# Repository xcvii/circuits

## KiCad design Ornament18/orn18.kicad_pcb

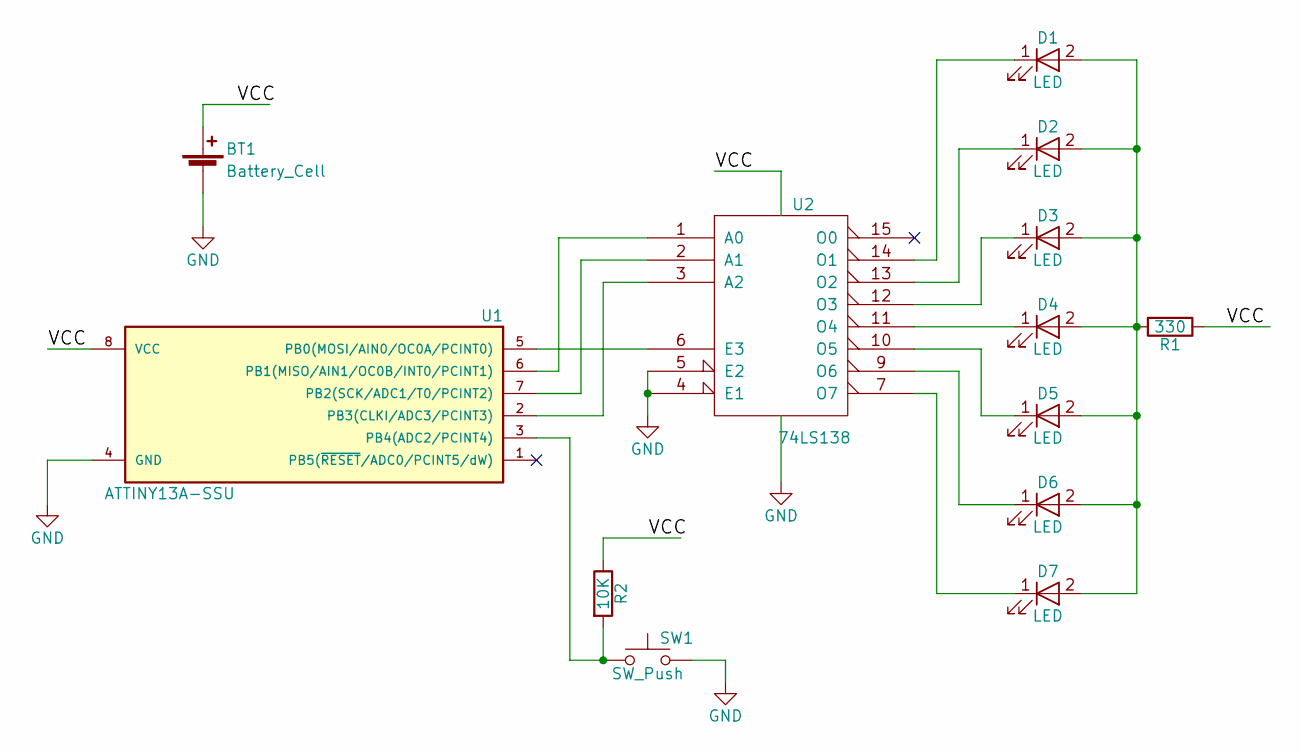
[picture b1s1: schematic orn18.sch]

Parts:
BT1: Battery_Cell; Keystone_3035
D1, D2, D3, D4, D5, D6, D7: LED; LED_0805_HandSoldering
R1: 330; R_0805_HandSoldering
R2: 10K; R_0805_HandSoldering
SW1: SW_Push; Tactile_Switch_6mm_x_6mm
U1: ATTINY13A-SSU; SOIC-8_3.9x4.9mm_Pitch1.27mm
U2: 74LS138; SOIC-16_3.9x9.9mm_Pitch1.27mm

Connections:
GND: BT1.2 (-), SW1.2, U1.4 (GND), U2.4 (E1), U2.5 (E2), U2.8 (GND)
unnamed: D1.1 (K), U2.14 (O1)
unnamed: D1.2 (A), D2.2 (A), D3.2 (A), D4.2 (A), D5.2 (A), D6.2 (A), D7.2 (A), R1.2
unnamed: D2.1 (K), U2.13 (O2)
unnamed: D3.1 (K), U2.12 (O3)
unnamed: D4.1 (K), U2.11 (O4)
unnamed: D5.1 (K), U2.10 (O5)
unnamed: D6.1 (K), U2.9 (O6)
unnamed: D7.1 (K), U2.7 (O7)
unnamed: R2.2, SW1.1, U1.3 (PB4(ADC2/PCINT4))
unnamed: U1.2 (PB3(CLKI/ADC3/PCINT3)), U2.3 (A2)
unnamed: U1.5 (PB0(MOSI/AIN0/OC0A/PCINT0)), U2.6 (E3)
unnamed: U1.6 (PB1(MISO/AIN1/OC0B/INT0/PCINT1)), U2.1 (A0)
unnamed: U1.7 (PB2(SCK/ADC1/T0/PCINT2)), U2.2 (A1)
VCC: BT1.1 (+), R1.1, R2.1, U1.8 (VCC), U2.16 (VCC)

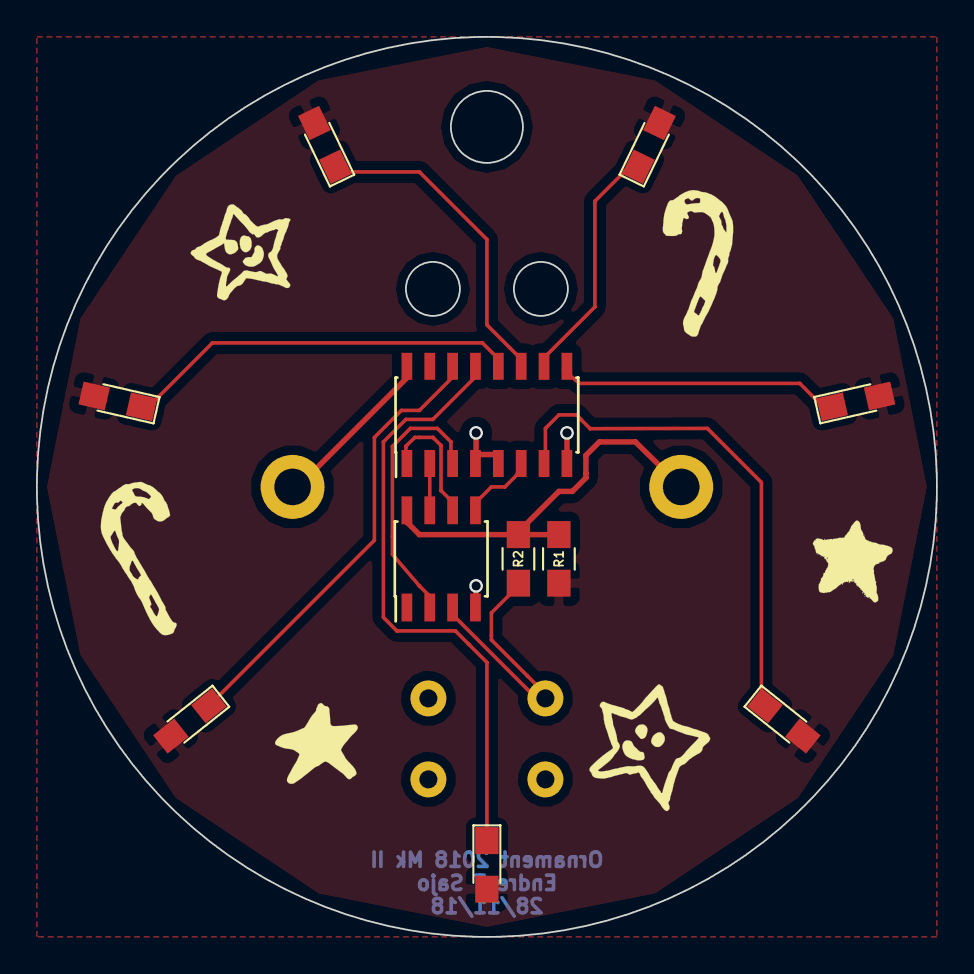
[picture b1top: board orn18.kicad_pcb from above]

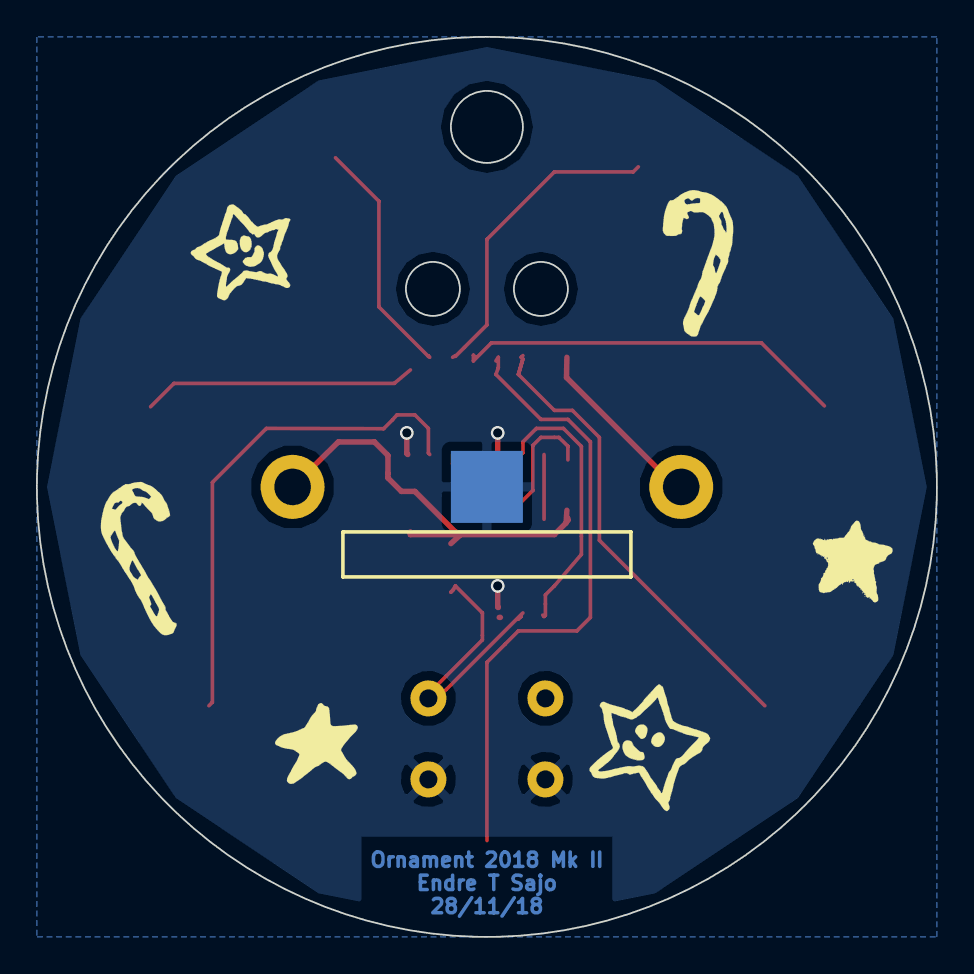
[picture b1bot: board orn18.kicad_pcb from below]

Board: 2 copper layers, 50.0 x 50.0 mm, 13 parts (2 on the bottom side), 15 nets.

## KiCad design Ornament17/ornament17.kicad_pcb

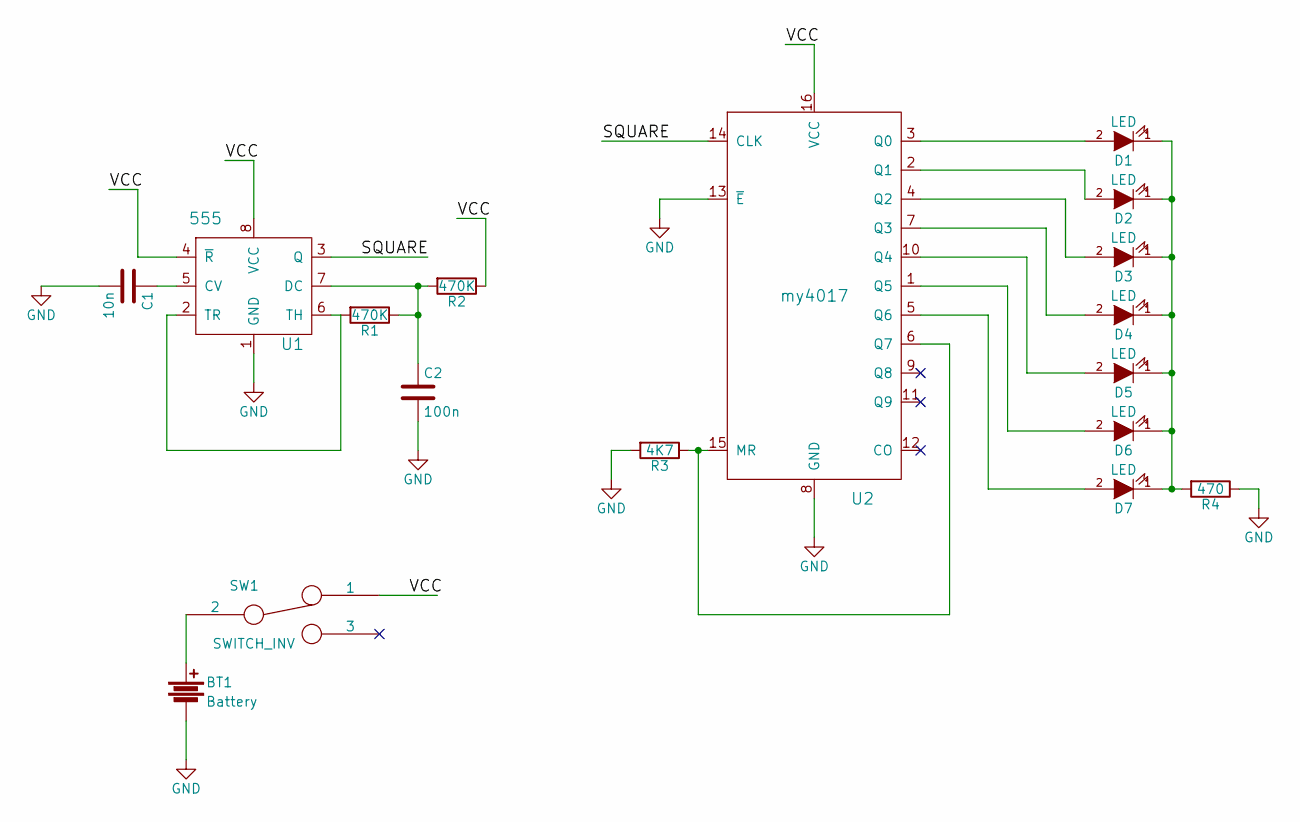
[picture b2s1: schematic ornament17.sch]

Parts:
BT1: Battery; 20mm_battery_clip
C1: 10n; C_0805_HandSoldering
C2: 100n; C_0805_HandSoldering
D1, D2, D3, D4, D5, D6, D7: LED; LED_0805_HandSoldering
R1, R2: 470K; R_0805_HandSoldering
R3: 4K7; R_0805_HandSoldering
R4: 470; R_0805_HandSoldering
SW1: SWITCH_INV; SPDT
U1: 555; SOIC-8_3.9x4.9mm_Pitch1.27mm
U2: my4017; SOIC-16_3.9x9.9mm_Pitch1.27mm

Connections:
/SQUARE: U1.3 (Q), U2.14 (CLK)
/VCC: R2.1, SW1.1, U1.4 (~R), U1.8 (VCC), U2.16 (VCC)
GND: BT1.2, C1.2, C2.2, R3.2, R4.1, U1.1 (GND), U2.8 (GND), U2.13 (~E)
unnamed: BT1.1, SW1.2
unnamed: C1.1, U1.5 (CV)
unnamed: C2.1, R1.1, R2.2, U1.7 (DC)
unnamed: D1.1 (K), D2.1 (K), D3.1 (K), D4.1 (K), D5.1 (K), D6.1 (K), D7.1 (K), R4.2
unnamed: D1.2 (A), U2.3 (Q0)
unnamed: D2.2 (A), U2.2 (Q1)
unnamed: D3.2 (A), U2.4 (Q2)
unnamed: D4.2 (A), U2.7 (Q3)
unnamed: D5.2 (A), U2.10 (Q4)
unnamed: D6.2 (A), U2.1 (Q5)
unnamed: D7.2 (A), U2.5 (Q6)
unnamed: R1.2, U1.2 (TR), U1.6 (TH)
unnamed: R3.1, U2.6 (Q7), U2.15 (MR)

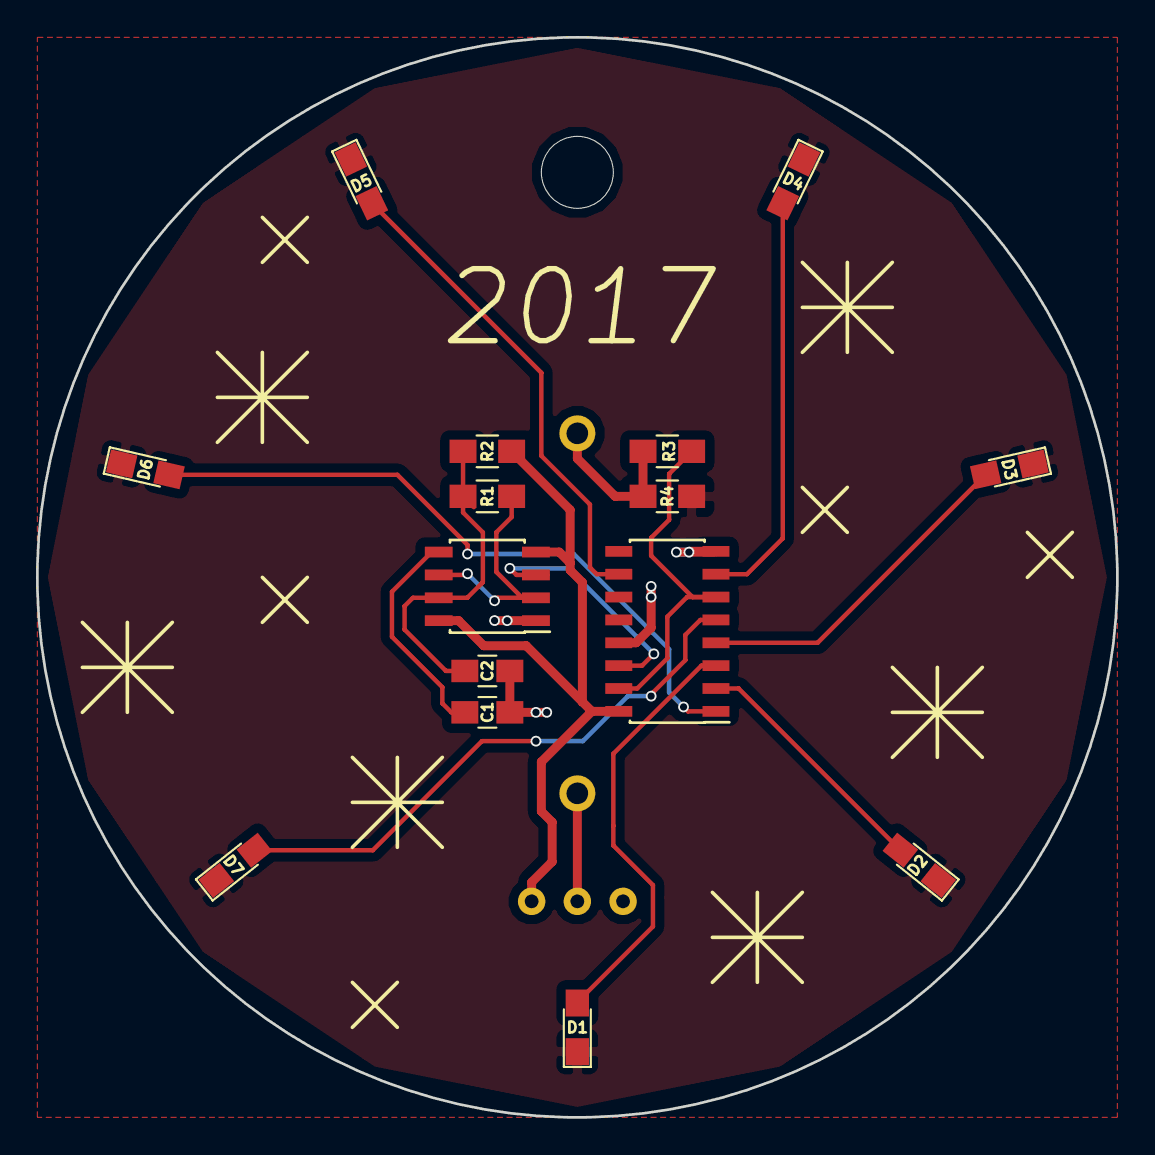
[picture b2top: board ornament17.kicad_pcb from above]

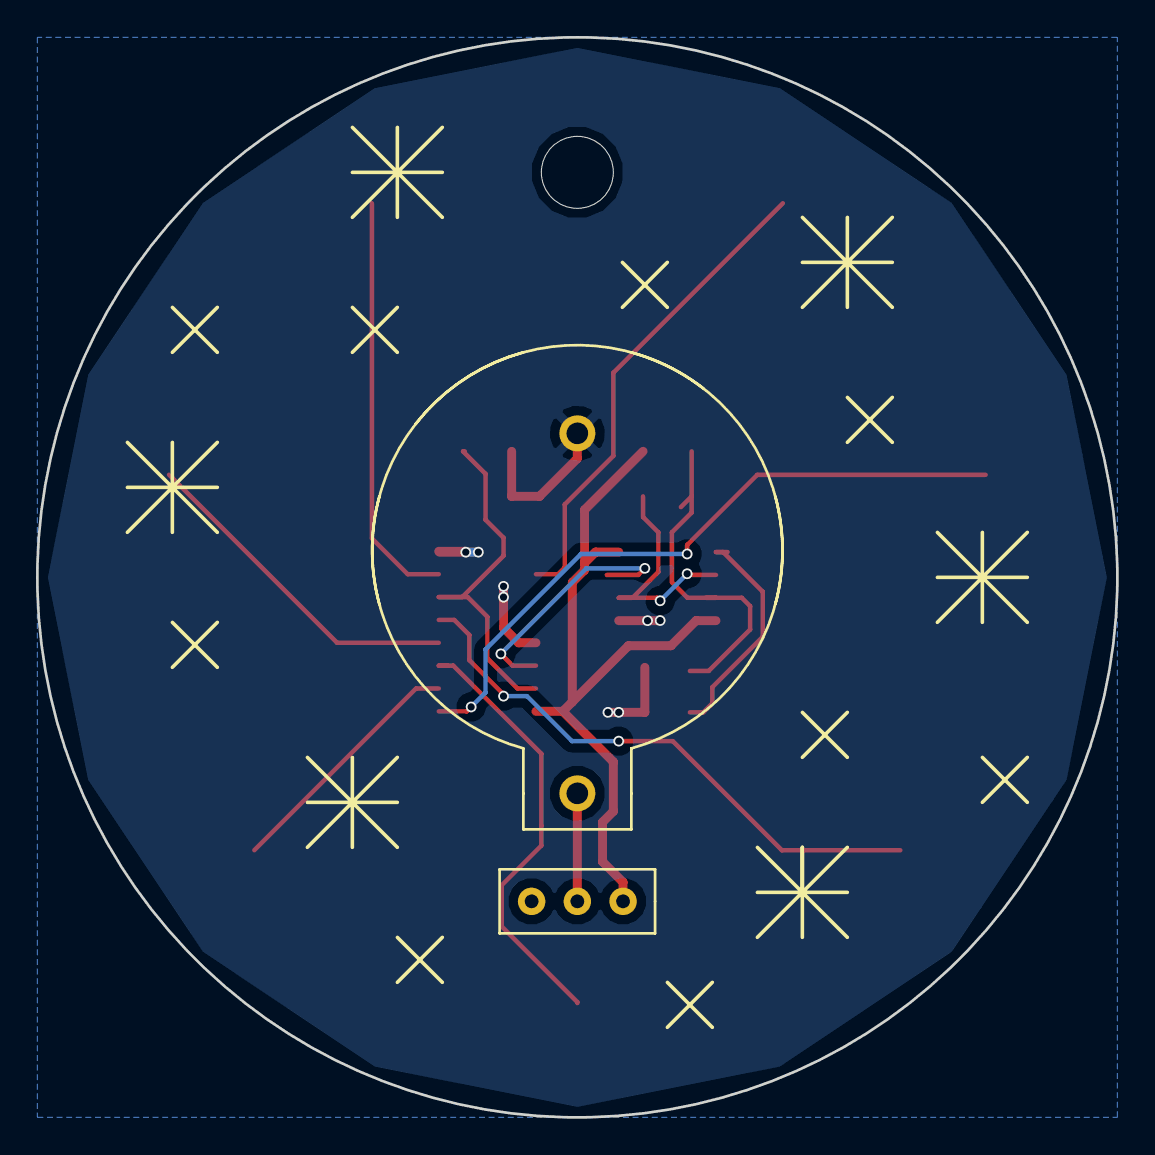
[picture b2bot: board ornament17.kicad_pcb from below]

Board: 2 copper layers, 60.0 x 60.0 mm, 17 parts (2 on the bottom side), 16 nets.

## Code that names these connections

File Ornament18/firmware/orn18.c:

#include <stdbool.h>

#include <util/delay.h>

#include <avr/interrupt.h>
#include <avr/io.h>
#include <avr/power.h>
#include <avr/sleep.h>
#include <avr/wdt.h>


bool g_running = false;


uint8_t LED_ADDRESS[] = {
    (0<<PB3) | (0<<PB2) | (1<<PB1),
    (0<<PB3) | (1<<PB2) | (0<<PB1),
    (0<<PB3) | (1<<PB2) | (1<<PB1),
    (1<<PB3) | (0<<PB2) | (0<<PB1),
    (1<<PB3) | (0<<PB2) | (1<<PB1),
    (1<<PB3) | (1<<PB2) | (0<<PB1),
    (1<<PB3) | (1<<PB2) | (1<<PB1),
};


#define delay_ms(time_ms) \
    do { \
    CLKPR = (1<<CLKPCE) | (1<<CLKPS3); \
    _delay_ms(time_ms); \
    CLKPR = (1<<CLKPCE); \
    } while (0)


void start_pwm(void)
{
    TCCR0A =
        (1<<COM0A1) | (0<<COM0A0) // clear on match, set on top
        | (1<<WGM01) | (1<<WGM00) // fast PWM
        ;

    TCCR0B =
        (0<<CS02) | (0<<CS01) | (1<<CS00) // no prescaling
        ;
}


void stop_pwm(void)
{
    TCCR0A = 0;
}


void set_pwm(int16_t intensity)
{
    if (intensity < 0)
    {
        OCR0A = 0;
    }
    else if (0x100 <= intensity)
    {
        OCR0A = 0xff;
    }
    else
    {
        OCR0A = (uint8_t)intensity;
    }
}


void sleep_helper(bool schedule_wakeup)
{
    if (schedule_wakeup)
    {
        WDTCR =
            (1<<WDCE)
            | (0<<WDE) | (1<<WDTIE)                         // interrupt mode
            | (0<<WDP3) | (0<<WDP2) | (0<<WDP1) | (1<<WDP0) // 32ms
            ;
        wdt_reset();
    }

    set_sleep_mode(SLEEP_MODE_PWR_DOWN);
    sleep_enable();
    sleep_cpu();
}


void sleep(void)
{
    sleep_helper(true);
}


void wakeup(void)
{
    sleep_disable();
    wdt_reset();
    WDTCR = (1<<WDCE) | (0<<WDTIE); // stopped
}


ISR(WDT_vect)
{
    wakeup();
}


bool is_pressed(void)
{
    for (int i = 0; i < 4; ++i)
    {
        if (PINB & (1<<PB4))
        {
            return false;
        }

        delay_ms(10);
    }

    return true;
}


ISR(PCINT0_vect)
{
    if (is_pressed())
    {
        g_running = !g_running;

        if (g_running)
        {
            wakeup();
            start_pwm();
        }
        else
        {
            stop_pwm();
            PORTB = 0;
        }
    }
}


void init(void)
{
    // don't need adc or analog comparator
    power_adc_disable();
    ADCSRA = 0;
    ACSR = (1<<ACD);

    // PB4: switch
    // PB3, PB2, PB1: LED address
    // PB0: PWM
    DDRB = (0<<PB4) | (1<<PB3) | (1<<PB2) | (1<<PB1) | (1<<PB0);
    PORTB = 0;

    GIMSK = (1<<PCIE);
    PCMSK = (1<<PCINT4);

    sei();
}


void shutdown(void)
{
    sleep_helper(false);
}


void run_ee(void)
{
    uint8_t current_led;
    uint8_t led_order[] = {1,0,2,3,4,5,6};
    for (uint16_t i = 0; g_running && i < 4200; ++i)
    {
        current_led = led_order[i % 7];
        PORTB = LED_ADDRESS[current_led] | (1<<PB0);
        delay_ms(75);
    }
}


int main(void)
{
    uint8_t current_led = 0;
    uint8_t random = 0;
    uint8_t hold_count = 0;

    for (;;)
    {
        init();

        while(g_running)
        {
            PORTB = LED_ADDRESS[current_led];

            uint8_t next_led = 0;
            do
            {
                random = 5 * random + 13;
                next_led = random % 7;
            }
            while (current_led == next_led);

            current_led = next_led;

            start_pwm();

            int16_t pwm_intensity = 0;

            for (int i = 0; i < 64; ++i)
            {
                pwm_intensity += 4;
                set_pwm(pwm_intensity);
                delay_ms(5);
            }

            sleep();

            for (int i = 0; i < 64; ++i)
            {
                pwm_intensity -= 4;
                set_pwm(pwm_intensity);
                delay_ms(5);
            }

            stop_pwm();

            sleep();

            if (!(PINB & (1<<PB4)))
            {
                if (17 <= ++hold_count)
                {
                    run_ee();
                    PORTB = 0;
                }
            }
            else
            {
                hold_count = 0;
            }
        }

        shutdown();
    }
}

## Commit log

2018-11-21 first stab at orn18 firmware
2018-11-23 no need to cycle interrupts
2018-11-24 add kicad project
2018-11-25 add mechanical holes; add .gitignore
2018-11-25 use standard bool
2018-11-26 fix mechanical holes; add placeholder for allpcb id
2018-11-27 remove silk screen; add signature
2018-11-28 bring ics closer together
2018-11-28 add silk screen
2018-11-29 change mechanical holes to round from oval
2018-12-02 debounce switch
2018-12-02 some clean up
2018-12-02 some more clean-up
2018-12-02 asdf
2018-12-05 easter egg
2018-12-08 fix glitch
2018-12-08 scale down clock for all delays
